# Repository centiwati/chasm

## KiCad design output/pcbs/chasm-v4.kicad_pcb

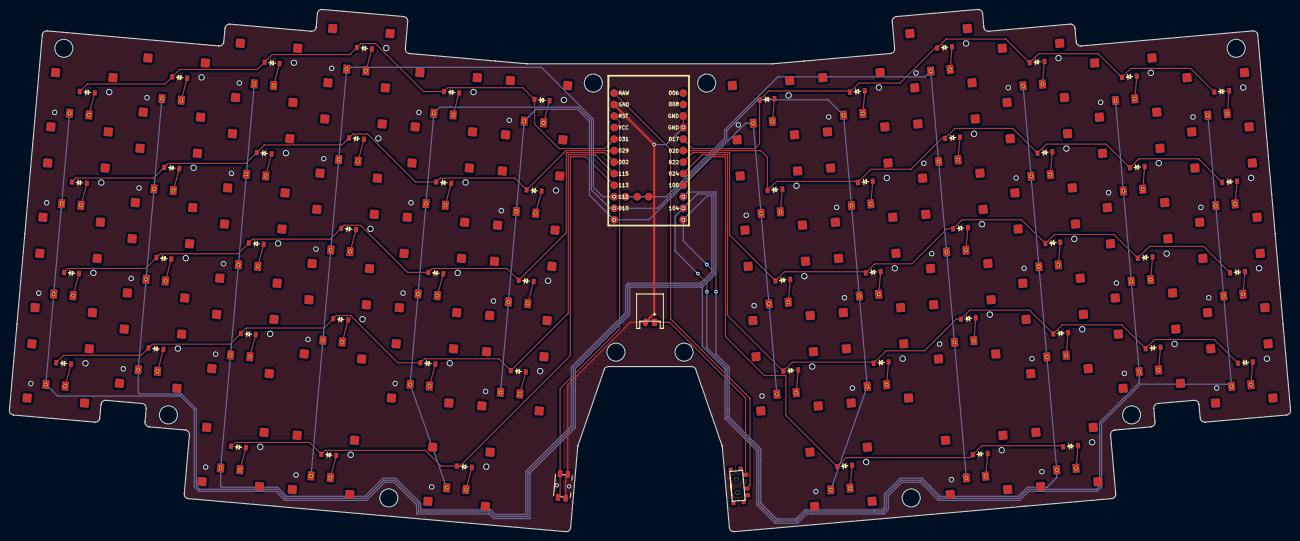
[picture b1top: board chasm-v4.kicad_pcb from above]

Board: 2 copper layers, 282.4 x 115.1 mm, 112 parts (0 on the bottom side), 74 nets.

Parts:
B1: Panasonic_EVQPUL_EVQPUC
D1, D2, D3, D4, D5, D6, D7, D8, D9, D10, D11, D12, D13, D14, D15, D16, D17, D18, D19, D20, D21, D22, D23, D24, D25, D26, D27, D28, D29, D30, D31, D32, D33, D34, D35, D36, D37, D38, D39, D40, D41, D42, D43, D44, D45, D46, D47, D48, D49, D50, D51, D52, D53, D54: diode_tht_sod123
JST1: JST_PH_S2B-PH-K_02x2.00mm_Angled
MCU1: nice_nano
S1, S2, S3, S4, S5, S6, S7, S8, S9, S10, S11, S12, S13, S14, S15, S16, S17, S18, S19, S20, S21, S22, S23, S24, S25, S26, S27, S28, S29, S30, S31, S32, S33, S34, S35, S36, S37, S38, S39, S40, S41, S42, S43, S44, S45, S46, S47, S48, S49, S50, S51, S52, S53, S54: PG1316S
T1: SPDT_C128955

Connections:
GND: B1.1, JST1.2, MCU1.3, MCU1.4, MCU1.23
P002: D2.1, D6.1, D10.1, D14.1, D18.1, D22.1, MCU1.18
P009: MCU1.13, S21.1, S22.1, S23.1, S24.1, S48.1, S49.1, S50.1, S51.1
P010: MCU1.14, S17.1, S18.1, S19.1, S20.1, S27.1, S44.1, S45.1, S46.1, S47.1, S54.1
P011: MCU1.10, S1.1, S2.1, S3.1, S4.1, S28.1, S29.1, S30.1, S31.1
P017: D31.1, D35.1, D39.1, D43.1, D47.1, D51.1, MCU1.5
P020: D30.1, D34.1, D38.1, D42.1, D46.1, D50.1, MCU1.6
P022: D29.1, D33.1, D37.1, D41.1, D45.1, D49.1, MCU1.7
P024: D28.1, D32.1, D36.1, D40.1, D44.1, D48.1, MCU1.8
P029: D3.1, D7.1, D11.1, D15.1, D19.1, D23.1, MCU1.19
P031: D4.1, D8.1, D12.1, D16.1, D20.1, D24.1, MCU1.20
P100: D52.1, D53.1, D54.1, MCU1.9
P104: MCU1.11, S5.1, S6.1, S7.1, S8.1, S32.1, S33.1, S34.1, S35.1
P106: MCU1.12, S9.1, S10.1, S11.1, S12.1, S25.1, S36.1, S37.1, S38.1, S39.1, S52.1
P111: MCU1.15, S13.1, S14.1, S15.1, S16.1, S26.1, S40.1, S41.1, S42.1, S43.1, S53.1
P113: D25.1, D26.1, D27.1, MCU1.16
P115: D1.1, D5.1, D9.1, D13.1, D17.1, D21.1, MCU1.17
RAW: MCU1.24, T1.2
RST: B1.2, MCU1.22
command_thumbrow: D26.2, S26.2
index_bottom: D17.2, S17.2
index_home: D18.2, S18.2
index_num: D20.2, S20.2
index_top: D19.2, S19.2
inner_bottom: D21.2, S21.2
inner_home: D22.2, S22.2
inner_num: D24.2, S24.2
inner_top: D23.2, S23.2
middle_bottom: D13.2, S13.2
middle_home: D14.2, S14.2
middle_num: D16.2, S16.2
middle_top: D15.2, S15.2
mirror_command_thumbrow: D53.2, S53.2
mirror_index_bottom: D44.2, S44.2
mirror_index_home: D45.2, S45.2
mirror_index_num: D47.2, S47.2
mirror_index_top: D46.2, S46.2
mirror_inner_bottom: D48.2, S48.2
mirror_inner_home: D49.2, S49.2
mirror_inner_num: D51.2, S51.2
mirror_inner_top: D50.2, S50.2
mirror_middle_bottom: D40.2, S40.2
mirror_middle_home: D41.2, S41.2
mirror_middle_num: D43.2, S43.2
mirror_middle_top: D42.2, S42.2
mirror_option_thumbrow: D52.2, S52.2
mirror_outer_bottom: D28.2, S28.2
mirror_outer_home: D29.2, S29.2
mirror_outer_num: D31.2, S31.2
mirror_outer_top: D30.2, S30.2
mirror_pinky_bottom: D32.2, S32.2
mirror_pinky_home: D33.2, S33.2
mirror_pinky_num: D35.2, S35.2
mirror_pinky_top: D34.2, S34.2
mirror_ring_bottom: D36.2, S36.2
mirror_ring_home: D37.2, S37.2
mirror_ring_num: D39.2, S39.2
mirror_ring_top: D38.2, S38.2
mirror_space1_thumbrow: D54.2, S54.2
option_thumbrow: D25.2, S25.2
outer_bottom: D1.2, S1.2
outer_home: D2.2, S2.2
outer_num: D4.2, S4.2
outer_top: D3.2, S3.2
pinky_bottom: D5.2, S5.2
pinky_home: D6.2, S6.2
pinky_num: D8.2, S8.2
pinky_top: D7.2, S7.2
pos: JST1.1, T1.1
ring_bottom: D9.2, S9.2
ring_home: D10.2, S10.2
ring_num: D12.2, S12.2
ring_top: D11.2, S11.2
space1_thumbrow: D27.2, S27.2

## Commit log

2025-05-27 added the stuff
2025-06-06 final version... for now
